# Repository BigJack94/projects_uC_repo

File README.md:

# projects_uC_repo
Repository with my projects - electronics circuits with microcontrollers (AVR and ESP8266).

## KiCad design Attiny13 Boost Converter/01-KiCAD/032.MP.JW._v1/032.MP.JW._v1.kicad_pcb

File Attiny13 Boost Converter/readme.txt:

Attiny13 Boost Converter - parameters:
-supply by 5V (e.g. USB) or 3,7 (Li-ion), any voltage supported by Attiny13 is acceptable
-two code solutions (with and without PID)
-PID need more memory, but is better under current load
-default output voltage is set by code and potentiometer
-KiCAD files include PCB project
-current output is 0,5 A (but is easy to change - need stronger elements)

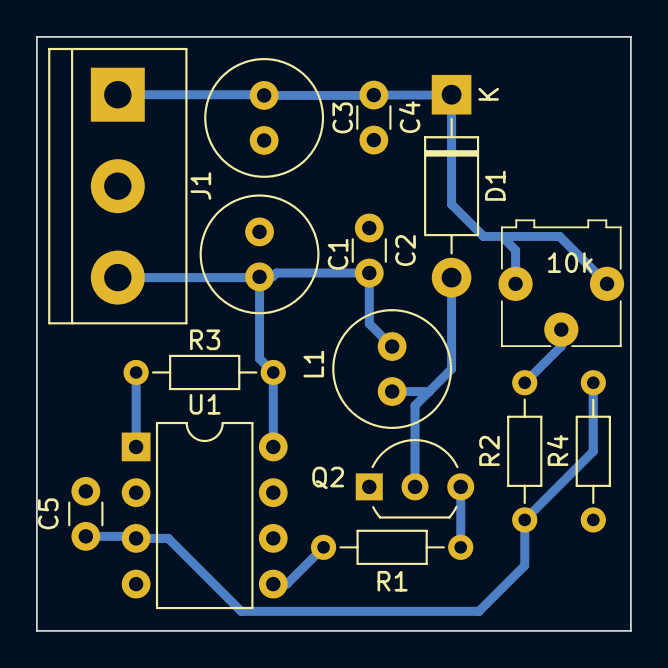
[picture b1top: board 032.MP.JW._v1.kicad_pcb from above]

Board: 2 copper layers, 33.0 x 33.0 mm, 15 parts (0 on the bottom side), 9 nets.

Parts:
C1, C3: 100u; C_Radial_D6.3mm_H5.0mm_P2.50mm
C2, C4, C5: 100n; C_Disc_D3.0mm_W1.6mm_P2.50mm
D1: 1N5818; D_DO-41_SOD81_P10.16mm_Horizontal
J1: Screw_Terminal_01x03; TerminalBlock_bornier-3_P5.08mm
L1: 100u; C_Radial_D6.3mm_H5.0mm_P2.50mm
Q2: BC639; TO-92L_Inline_Wide
R1: 1k; R_Axial_DIN0204_L3.6mm_D1.6mm_P7.62mm_Horizontal
R2: 4,6k; R_Axial_DIN0204_L3.6mm_D1.6mm_P7.62mm_Horizontal
R3: 10k; R_Axial_DIN0204_L3.6mm_D1.6mm_P7.62mm_Horizontal
R4: 460; R_Axial_DIN0204_L3.6mm_D1.6mm_P7.62mm_Horizontal
RV1: 10k; potentiometer_3362P
U1: ATtiny13V-10SS; DIP-8_W7.62mm

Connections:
GND: C1.1, C2.1, C3.2, C4.2, C5.2, J1.2, Q2.1 (E), R4.1, U1.4 (GND)
unnamed: D1.2 (A), L1.2 (-), Q2.2 (C)
unnamed: Q2.3 (B), R1.1
unnamed: R2.2, RV1.1
unnamed: R1.2, U1.5 (PB0)
unnamed: C5.1, R2.1, R4.2, U1.3 (PB4)
unnamed: R3.2, U1.1 (~RESET/PB5)
VCC: C1.2, C2.2, J1.3, L1.1 (+), R3.1, U1.8 (VCC)
VCCQ: C3.1, C4.1, D1.1 (K), J1.1, RV1.2, RV1.3

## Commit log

2023-08-31 weather station added
2024-01-24 Added Bicycle Light and USB Controller
2024-01-24 added new points
2024-02-08 tested usb charger - ok, work
2024-03-23 Added few function, removed bugs
2024-04-28 new concept
2024-04-28 Added Automatic Watering Time Station
2024-07-25 added new project
    Attiny13 boost converter
2024-11-02 new project was created
2024-11-03 update
    new folders, add more abour function generator
2024-11-06 Function Generator With Voltage Converter update
    added code, calculations and simulations files
2024-11-17 Function Generator With Voltage Converter
    added images and edited description
2025-01-21 portable soldering station
2025-01-22 033 update
2025-01-22 update_description
2025-10-23 portable station update
2025-10-24 description
2025-10-25 add code
